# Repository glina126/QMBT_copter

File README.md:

# QMBT_copter
A simple, yet versatile quadcopter controller and code. Based on the Arduino platform using the Atmega328p and MPU6050.

 |align=center]

##Final Update:
This project is changing direction. The atmega328p microcontroller is simply insufficient for being used as a quadcopter brain. <br>
This is due to a few reasons mainly because - not enough interrupts and 8bit architecture.  <br>
The loop runs at a mere 33 miliseconds, which is not sufficient.  <br>
Also, due to the lack of interrupts, the precision at which we can sample the RC RX is very low causing noise in the system. <br>
That being said, the project is changing gears and moving on to a much better microcontroller, LPC11U35 Cortex-m0 running at 48mhz. <br> 

###This project has a few milestones that are set on its path. 
1. Create a versatile PCB which will overcome the common problems such as power distribution. 
2. Create lightweight code that will be self sufficient, aka, no external program will be needed for changing settings of the quadcopter, except for a terminal window. 
3. Ultimate goal is to have full support of peripheral devices such as a sonic distance sensor to help aid in obstacle avoidance, or a GPS unit for man-less operation. 

This is just the beginning of the project, though experimentation with the PCB have been conducted for a while now. At this point, the project is reset to a fresh start.

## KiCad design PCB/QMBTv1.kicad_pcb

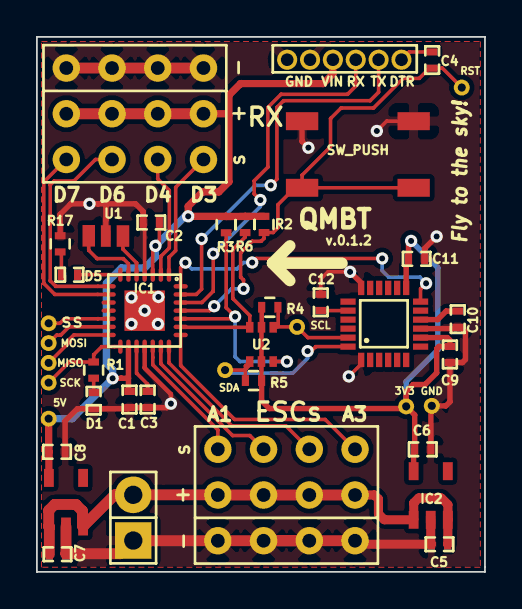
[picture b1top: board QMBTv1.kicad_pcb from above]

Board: 2 copper layers, 24.9 x 29.7 mm, 42 parts (0 on the bottom side), 33 nets.

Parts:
C1, C2, C3, C4, C10, C11: 0.1uF; SMD-0402_c
C5: 1uF; SMD-0402_c
C6: 2.2uF; SMD-0402_c
C7, C8: C; SMD-0402_c
C9: 10nF; SMD-0402_c
C12: 2.2nF; SMD-0402_c
C13: 6pin_1.27mm
D1, D5: LED; SMD-0402_LED
IC1: ATMEGA328P-MM; QFN-28-4x4mm_fixed_mask
IC2, IC3: MCP1802_(Vreg); Sot-23-5
IC4: MPU6050
P9: MISO; 1x0.5mm_Through_hole2
P10: MOSI; 1x0.5mm_Through_hole2
P11: SCK; 1x0.5mm_Through_hole2
P12: RST; 1x0.5mm_Through_hole2
P14: SDA; 1x0.5mm_Through_hole2
P15: SCL; 1x0.5mm_Through_hole2
P16: SS; 1x0.5mm_Through_hole2
P17: VCC; Socket_Strip_Straight_1x02
P18: 3V3; 1x0.5mm_Through_hole2
P19: GND; 1x0.5mm_Through_hole2
P20: 5V; 1x0.5mm_Through_hole2
R1, R3, R4, R5, R6, R17: 1K; R_0402
R2: 10K; R_0402
SW1: SW_PUSH; switch_tactile_SM10
U1: ceramic_resonator; ceramic_resonator_smd
U2: BSS138DW_array
U3, U4: conn_3x4

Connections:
+3.3V: C6.1, C9.1, C11.1, IC2.5, IC4.8, IC4.13, P18.1, R4.1, R5.1, U2.2, U2.5
+5V: C1.1, C2.1, C8.1, C13.3, IC1.3, IC1.16, IC3.5, P20.1, R2.1, R3.1, R6.1, U3.5
A0: IC1.19, U4.1
A1: IC1.20, U4.2
A2: IC1.21, U4.3
A3: IC1.22, U4.4
D2: IC1.28, IC4.12
D3: IC1.1, U3.1
D4: IC1.2, U3.2
D5: D5.1, IC1.7
D6: IC1.8, U3.3
D7: IC1.9, U3.4
D10: IC1.12, P16.1
DTR: C4.1, C13.6
GND: C1.2, C2.2, C3.2, C5.2, C6.2, C7.2, C8.2, C9.2, C10.2, C11.2, C12.2, C13.1, C13.2, D1.2, IC1.4, IC1.18, IC1.d29, IC2.2, IC3.2, IC4.1, IC4.9, IC4.18, P17.1, P19.1, R17.1, SW1.2, U1.3, U3.6, U4.6
H_SCL: IC1.24, R3.2, U2.6
H_SDA: IC1.23, R6.2, U2.3
MISO: IC1.14, P9.1
MOSI: IC1.13, P10.1
unnamed: C3.1, IC1.17
unnamed: C10.1, IC4.10
unnamed: C12.1, IC4.20
unnamed: D1.1, R1.1
unnamed: D5.2, R17.2
unnamed: IC1.5, U1.1
unnamed: IC1.6, U1.2
RESET: C4.2, IC1.25, P12.1, R2.2, SW1.1
RXI: C13.4, IC1.26
SCK: IC1.15, P11.1, R1.2
SCL: IC4.23, P15.1, R4.2, U2.1
SDA: IC4.24, P14.1, R5.2, U2.4
TXD: C13.5, IC1.27
VIN: C5.1, C7.1, IC2.1, IC2.3, IC3.1, IC3.3, P17.2, U4.5

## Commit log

2015-01-12 introductory text
2015-01-12 added <br> to have proper line spacing
2015-02-22 initial commit. definitions and a simple relay mechanism
2015-02-22 QMBT big v.0.1 PCB
2015-02-22 added mpu6050 support and wrapped display modules in #if endif statements
2015-02-22 added channel inversion and comments
2015-02-22 added a complementary filter and separated the IMU call into its own function
2015-02-22 finalized get user input function
2015-02-22 added a PID algorithm
2015-02-23 added an arming mechanism
2015-03-22 final touches and tweaks and it finally flies!!!!
2015-03-22 Revert "added <br> to have proper line spacing"
    This reverts commit 8e18c9814b96ebf0a9419dbbde5b1e4513496d16.
2015-03-22 fixed commit issue
2015-03-22 cleaned up comments
2015-03-22 added citations and a project description + future plans
2015-03-28 more PID tunning
2015-03-28 removed commercial
2015-03-28 removed link reference
2015-03-28 added one more gif
2015-03-28 fixed gif positions
2015-03-28 picture of the qmbt and the code in the background
2015-03-28 added an image of the QMBT
2015-03-28 added align center to the image
2015-03-28 revert align-center
